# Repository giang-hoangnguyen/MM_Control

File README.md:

# MM_Control

Board điều khiển chuyển động dùng STM32F407VET6, 100 × 100 mm, 2 lớp. Một board gồm 4 kênh động cơ DC (DRV8872), 3 socket driver bước TMC2209, cổng bus servo STS3215, USB-C (CDC), CAN và các header SPI, I2C, UART.

Repo gồm hồ sơ thiết kế (KiCad, Gerber, BOM), firmware, thư viện Python, vỏ in 3D và tài liệu hướng dẫn đặt mạch, mua linh kiện, hàn, kiểm tra, ứng dụng. Tác giả thiết kế: tue-minh. Chỉnh sửa và bổ sung: giang-hoangnguyen.

## Bắt đầu

1. Đọc hướng dẫn chi tiết tại [docs/MM_Control_Hướng dẫn.pdf](docs/MM_Control_H%C6%B0%E1%BB%9Bng%20d%E1%BA%ABn.pdf) và [docs/MM_Control_Hướng dẫn.pptx](docs/MM_Control_H%C6%B0%E1%BB%9Bng%20d%E1%BA%ABn.pptx).
2. Đặt PCB bằng [hardware/MM_Control_gerber.zip](hardware/MM_Control_gerber.zip): 2 lớp, 100 × 100 mm, 1,6 mm.
3. Mua linh kiện theo [hardware/BOM_MM_Control.csv](hardware/BOM_MM_Control.csv), thêm 3 module TMC2209, động cơ, nguồn, ST-Link, cáp USB-C dữ liệu.
4. Hàn theo 4 giai đoạn (nguồn 5 V, 3,3 V, MCU và USB, driver). Chỉnh RV1 cho TP3 = 5,0 V **trước khi** gắn linh kiện 5 V.
5. Nạp firmware (`firmware/build/Debug/MM_Control.bin` tại 0x08000000) bằng ST-Link qua J3.
6. Test từng khối bằng ví dụ Python trong `firmware/python/examples`.

## Cấp nguồn

| Mục | Giá trị | Cơ sở |
|---|---|---|
| VM dùng được | 6,5–28 V | DRV8872 ≥ 6,5 V, TMC2209 ≤ 28 V (datasheet) |
| Dòng chop mỗi kênh DC | khoảng 1,75 A | 0,35 V / 0,2 Ω (datasheet DRV8872, tự tính) |
| TMC2209 | 2 A RMS mỗi cuộn | datasheet |
| Buck 5 V | 3 A | datasheet TPS5430 |
| Servo STS3215 | bản 7,4 V: 4–7,4 V; có bản 12 V | datasheet Feetech; dùng chung rail VM |

Board không có mạch chống ngược cực trên VM. USB-C không cấp nguồn cho board.

## Cấu trúc thư mục

```
docs/        Hướng dẫn chi tiết (PDF, Word), slide hướng dẫn
hardware/    Gerber, BOM, schematic PDF, dự án KiCad 9
firmware/    Mã nguồn STM32 (CMake), thư viện Python, file .bin dựng sẵn
enclosure/   Vỏ in 3D: STL (hướng in), file Fusion, script dựng vỏ
images/      Ảnh dùng trong tài liệu
```

## Vỏ in 3D

Hộp hai mảnh, kẹp board bằng 4 vít M4 × 12 qua lỗ góc, 4 insert M4 trong trụ nắp. In PLA.

## Nguồn và giấy phép

- Datasheet: TI DRV8872, TPS5430; Trinamic TMC2209; Feetech STS3215 (liên kết trong tài liệu chi tiết, mục 9).
- Repo không kèm file LICENSE.

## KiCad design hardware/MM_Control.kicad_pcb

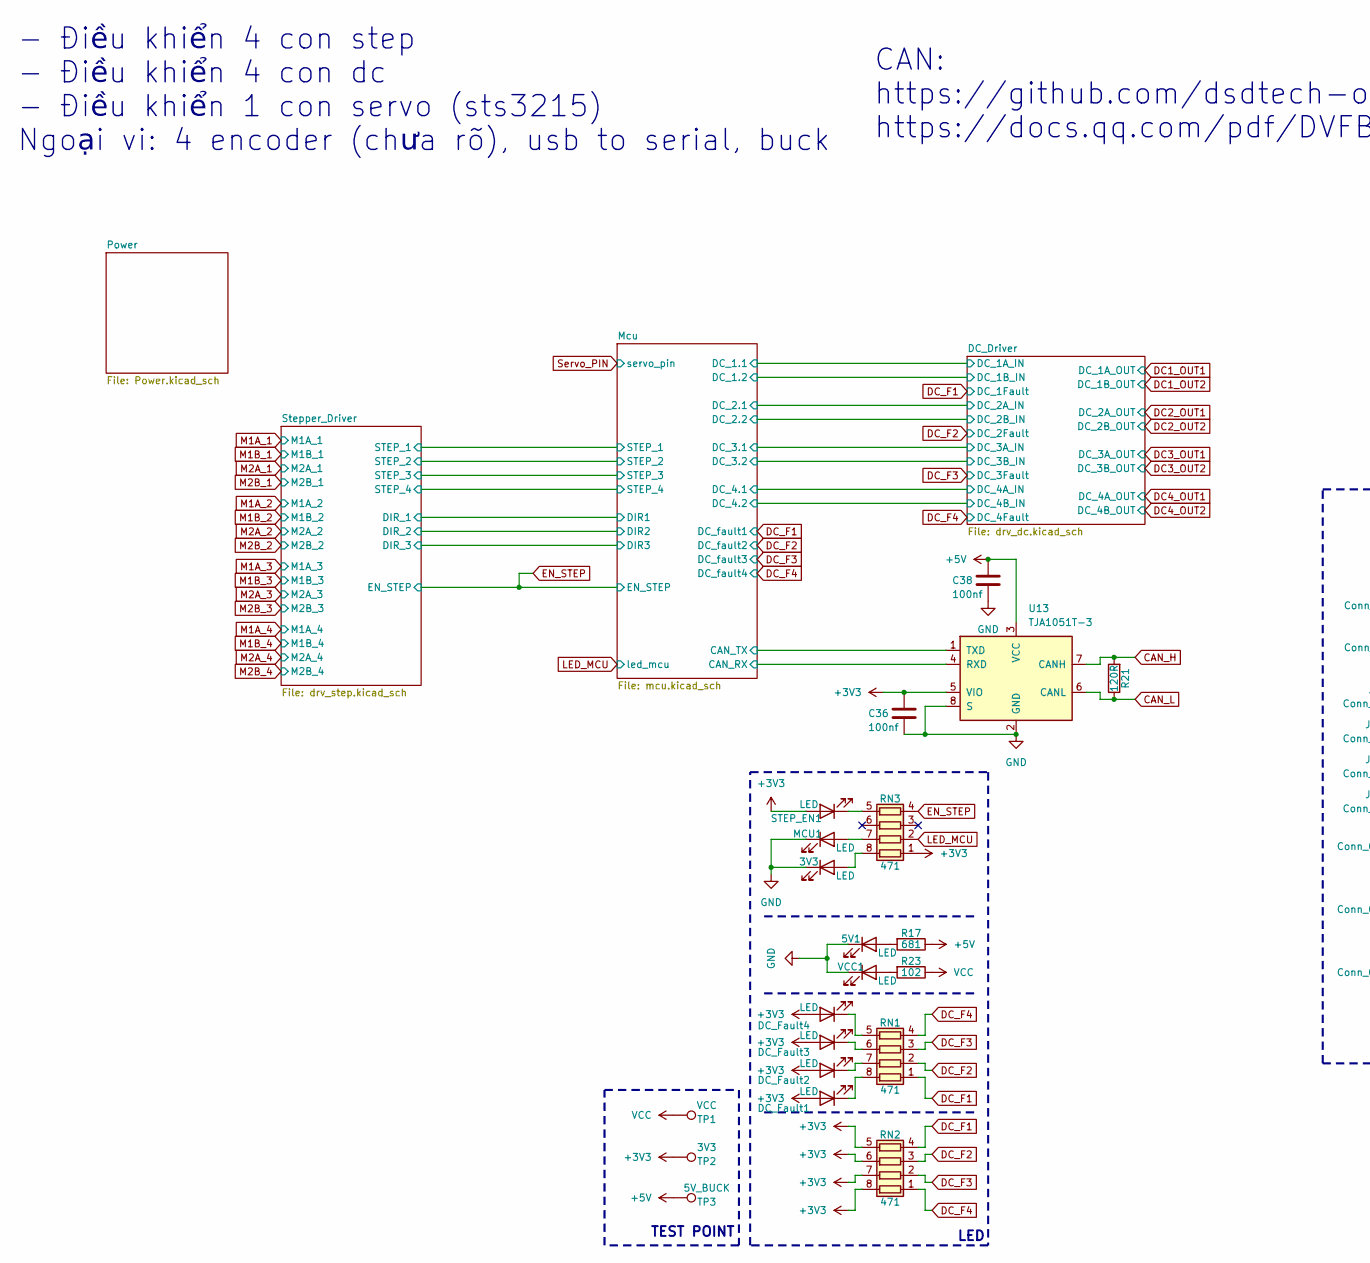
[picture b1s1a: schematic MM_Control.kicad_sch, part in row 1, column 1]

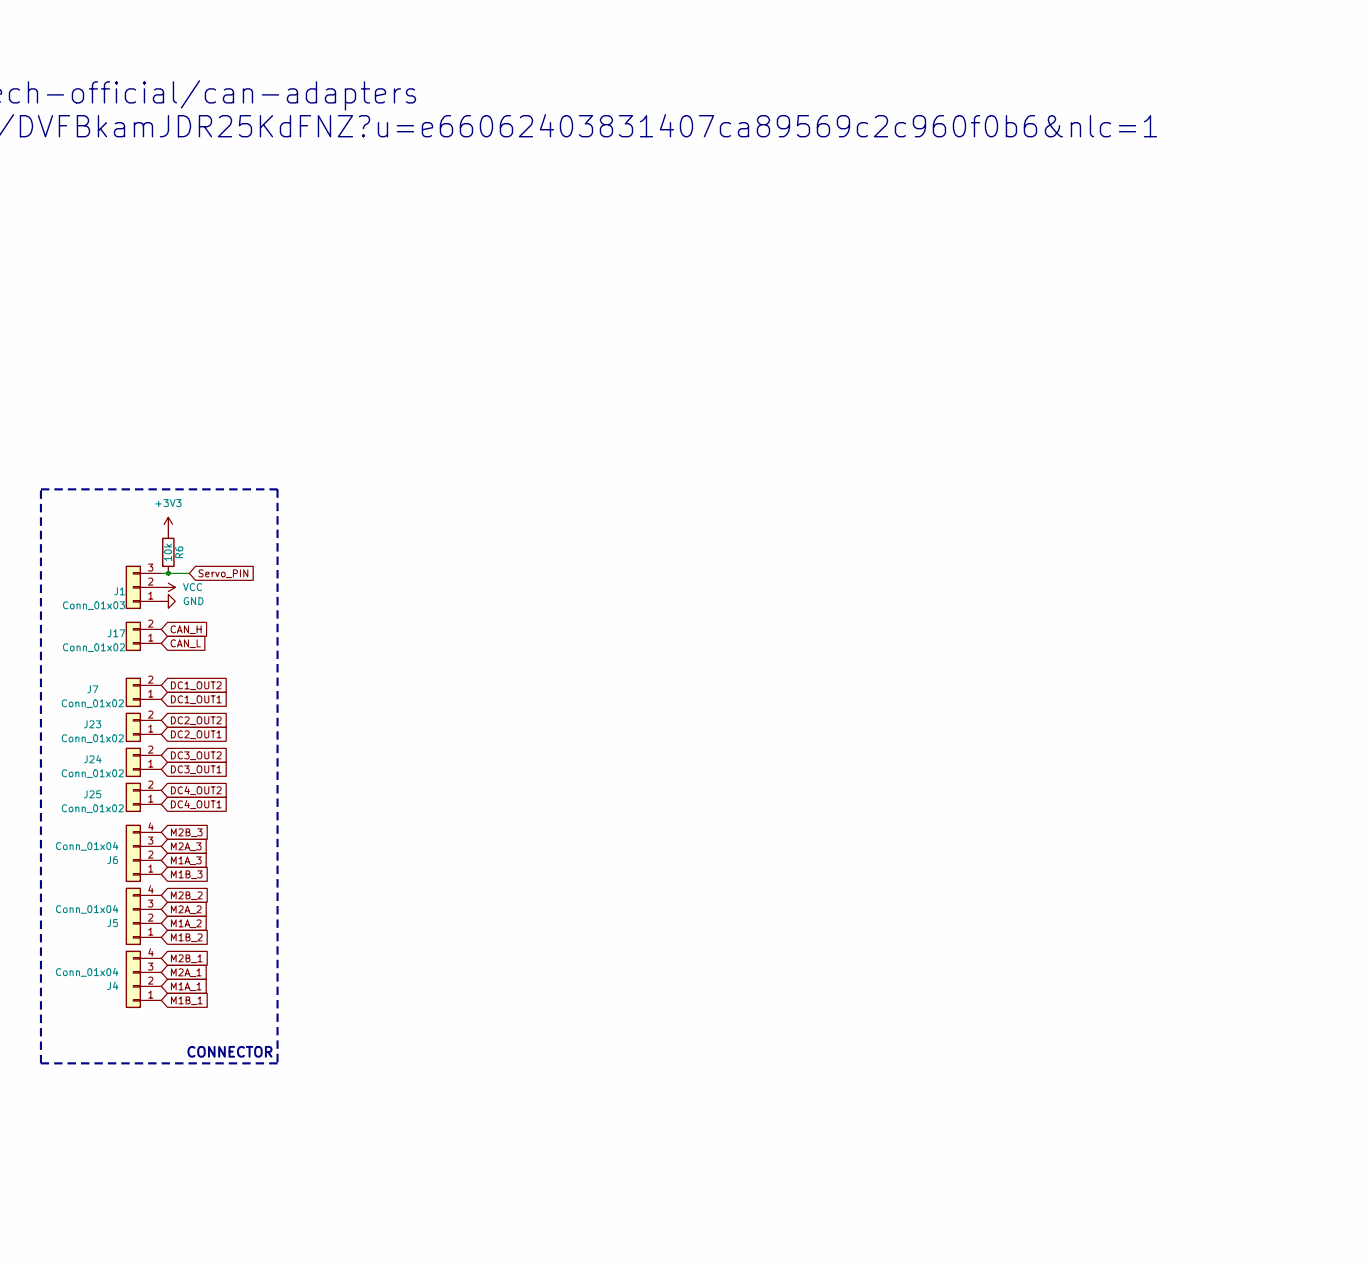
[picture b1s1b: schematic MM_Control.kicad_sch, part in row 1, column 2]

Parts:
3V3, 5V1: LED; LED_0603_1608Metric_Pad1.05x0.95mm_HandSolder
C36, C38: 100nf; C_0603_1608Metric_Pad1.08x0.95mm_HandSolder
DC_Fault1, DC_Fault2, DC_Fault3, DC_Fault4: LED; LED_0603_1608Metric_Pad1.05x0.95mm_HandSolder
J1: Conn_01x03; Molex_SPOX_5267-03A_1x03_P2.50mm_Vertical
J4, J5, J6: Conn_01x04; JST_XH_B4B-XH-A_1x04_P2.50mm_Vertical
J7, J23, J24, J25: Conn_01x02; TerminalBlock_Phoenix_MKDS-1,5-2-5.08_1x02_P5.08mm_Horizont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
J17: Conn_01x02; TerminalBlock_MaiXu_MX126-5.0-02P_1x02_P5.00mm
MCU1: LED; LED_0603_1608Metric_Pad1.05x0.95mm_HandSolder
R6: 10k; R_0603_1608Metric_Pad0.98x0.95mm_HandSolder
R17: 681; R_0603_1608Metric_Pad0.98x0.95mm_HandSolder
R21: 120R; R_0603_1608Metric_Pad0.98x0.95mm_HandSolder
R23: 102; R_0603_1608Metric_Pad0.98x0.95mm_HandSolder
RN1, RN2, RN3: 471; R_Array_Concave_4x0603
STEP_EN1: LED; LED_0603_1608Metric_Pad1.05x0.95mm_HandSolder
TP1: VCC; TestPoint_Pad_D2.0mm
TP2: 3V3; TestPoint_Pad_D2.0mm
TP3: 5V_BUCK; TestPoint_Pad_D2.0mm
U13: TJA1051T-3; SOIC-8_3.9x4.9mm_P1.27mm
VCC1: LED; LED_0603_1608Metric_Pad1.05x0.95mm_HandSolder

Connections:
+3V3: C36.2, DC_Fault1.2 (A), DC_Fault2.2 (A), DC_Fault3.2 (A), DC_Fault4.2 (A), R6.1, RN2.5 (R4.2), RN2.6 (R3.2), RN2.7 (R2.2), RN2.8 (R1.2), RN3.1 (R1.1), STEP_EN1.2 (A), TP2.1, U13.5 (VIO); also elsewhere on the board
+5V: C38.2, R17.1, TP3.1, U13.3 (VCC); also elsewhere on the board
/Mcu/CAN_RX: U13.4 (RXD); also elsewhere on the board
/Mcu/CAN_TX: U13.1 (TXD); also elsewhere on the board
CAN_H: J17.2, R21.2, U13.7 (CANH)
CAN_L: J17.1, R21.1, U13.6 (CANL)
DC1_OUT1: J7.1; also elsewhere on the board
DC1_OUT2: J7.2; also elsewhere on the board
DC2_OUT1: J23.1; also elsewhere on the board
DC2_OUT2: J23.2; also elsewhere on the board
DC3_OUT1: J24.1; also elsewhere on the board
DC3_OUT2: J24.2; also elsewhere on the board
DC4_OUT1: J25.1; also elsewhere on the board
DC4_OUT2: J25.2; also elsewhere on the board
DC_F1: RN1.1 (R1.1), RN2.4 (R4.1); also elsewhere on the board
DC_F2: RN1.2 (R2.1), RN2.3 (R3.1); also elsewhere on the board
DC_F3: RN1.3 (R3.1), RN2.2 (R2.1); also elsewhere on the board
DC_F4: RN1.4 (R4.1), RN2.1 (R1.1); also elsewhere on the board
EN_STEP: RN3.4 (R4.1); also elsewhere on the board
GND: 3V3.1 (K), 5V1.1 (K), C36.1, C38.1, J1.1, MCU1.1 (K), U13.2 (GND), U13.8 (S), VCC1.1 (K); also elsewhere on the board
LED_MCU: RN3.2 (R2.1); also elsewhere on the board
M1A_1: J4.2; also elsewhere on the board
M1A_2: J5.2; also elsewhere on the board
M1A_3: J6.2; also elsewhere on the board
M1B_1: J4.1; also elsewhere on the board
M1B_2: J5.1; also elsewhere on the board
M1B_3: J6.1; also elsewhere on the board
M2A_1: J4.3; also elsewhere on the board
M2A_2: J5.3; also elsewhere on the board
M2A_3: J6.3; also elsewhere on the board
M2B_1: J4.4; also elsewhere on the board
M2B_2: J5.4; also elsewhere on the board
M2B_3: J6.4; also elsewhere on the board
unnamed: 3V3.2 (A), RN3.8 (R1.2)
unnamed: 5V1.2 (A), R17.2
unnamed: DC_Fault1.1 (K), RN1.8 (R1.2)
unnamed: DC_Fault2.1 (K), RN1.7 (R2.2)
unnamed: DC_Fault3.1 (K), RN1.6 (R3.2)
unnamed: DC_Fault4.1 (K), RN1.5 (R4.2)
unnamed: MCU1.2 (A), RN3.7 (R2.2)
unnamed: RN3.5 (R4.2), STEP_EN1.1 (K)
unnamed: R23.2, VCC1.2 (A)
Servo_PIN: J1.3, R6.2; also elsewhere on the board
VM1: J1.2, R23.1, TP1.1; also elsewhere on the board

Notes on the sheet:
TEST POINT
CAN: https://github.com/dsdtech-official/can-adapters https://docs.qq.com/pdf/DVFBkamJDR25KdFNZ?u=e66062403831407ca89569c2c960f0b6&nlc=1
CONNECTOR
LED
- Điều khiển 4 con step - Điều khiển 4 con dc - Điều khiển 1 con servo (sts3215) Ngoại vi: 4 encoder (chưa rõ), usb to serial, buck

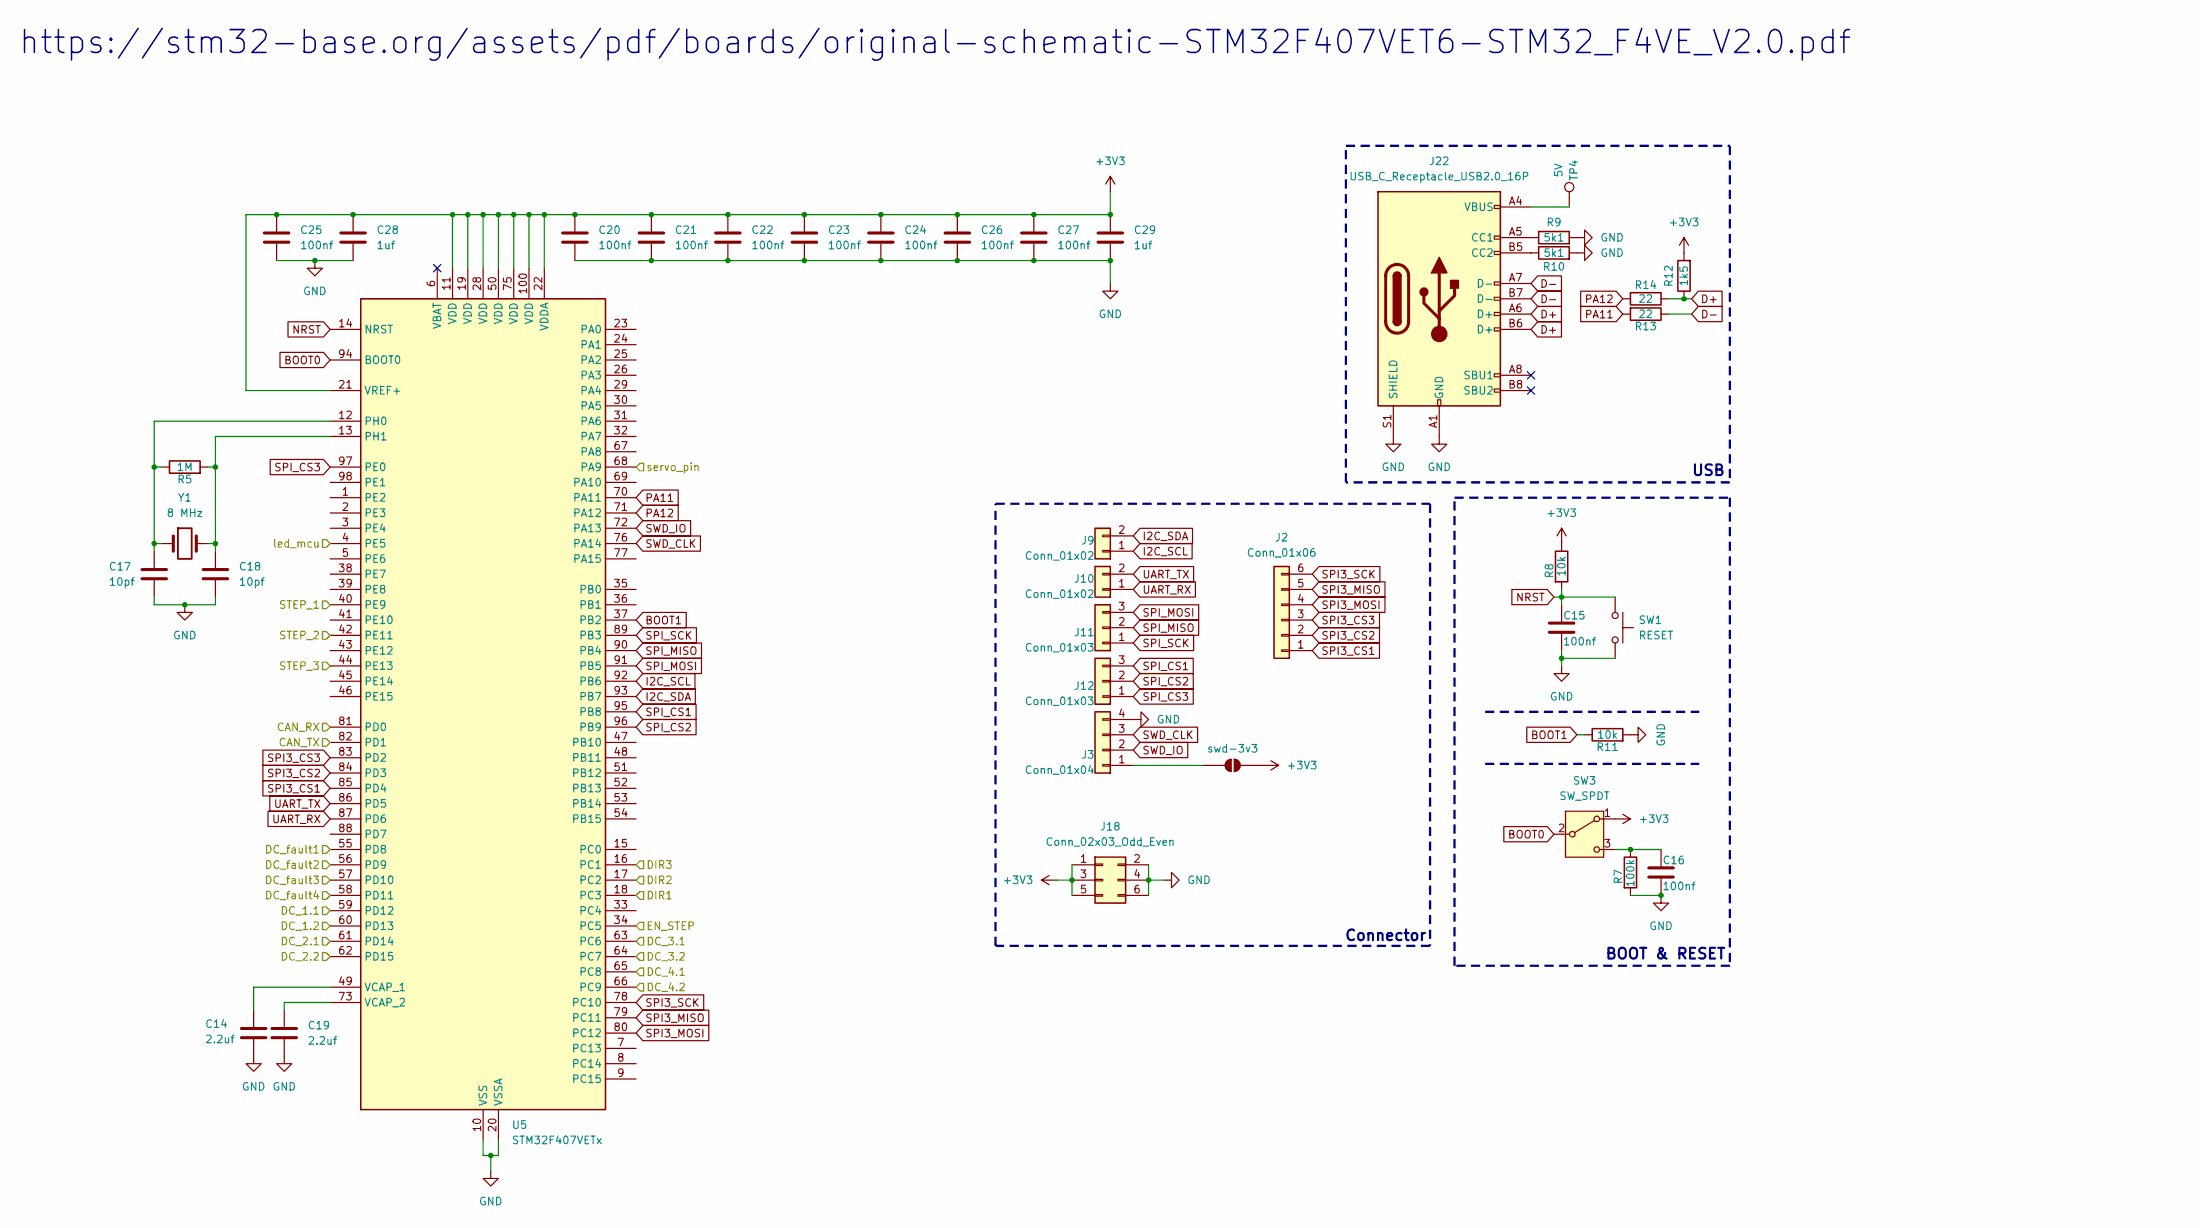
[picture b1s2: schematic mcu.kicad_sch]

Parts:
C14, C19: 2.2uf; C_0603_1608Metric_Pad1.08x0.95mm_HandSolder
C15, C16, C20, C21, C22, C23, C24, C25, C26, C27: 100nf; C_0603_1608Metric_Pad1.08x0.95mm_HandSolder
C17, C18: 10pf; C_0603_1608Metric_Pad1.08x0.95mm_HandSolder
C28, C29: 1uf; C_0603_1608Metric_Pad1.08x0.95mm_HandSolder
J2: Conn_01x06; PinHeader_1x06_P2.54mm_Vertical
J3: Conn_01x04; PinHeader_1x04_P2.54mm_Vertical
J9, J10: Conn_01x02; PinHeader_1x02_P2.54mm_Vertical
J11, J12: Conn_01x03; PinHeader_1x03_P2.54mm_Vertical
J18: Conn_02x03_Odd_Even; PinHeader_2x03_P2.54mm_Vertical
J22: USB_C_Receptacle_USB2.0_16P; USB_C_Receptacle_GCT_USB4105-xx-A_16P_TopMnt_Horizontal
R5: 1M; R_0603_1608Metric_Pad0.98x0.95mm_HandSolder
R7: 100k; R_0603_1608Metric_Pad0.98x0.95mm_HandSolder
R8, R11: 10k; R_0603_1608Metric_Pad0.98x0.95mm_HandSolder
R9, R10: 5k1; R_0603_1608Metric_Pad0.98x0.95mm_HandSolder
R12: 1k5; R_0603_1608Metric_Pad0.98x0.95mm_HandSolder
R13, R14: 22; R_0603_1608Metric_Pad0.98x0.95mm_HandSolder
SW1: RESET; tue_sw_smd_3x6x2.5mm
SW3: SW_SPDT; tue_SS12D00_3P_2.5mm
TP4: 5V; TestPoint_Pad_D2.0mm
U5: STM32F407VETx; LQFP-100_14x14mm_P0.5mm
Y1: 8 MHz; Crystal_HC49-4H_Vertical
swd-3v3: SolderJumper_2_Open; SolderJumper-2_P1.3mm_Open_RoundedPad1.0x1.5mm

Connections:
+3V3: C20.1, C21.1, C22.1, C23.1, C24.1, C25.1, C26.1, C27.1, C28.1, C29.1, J18.1, J18.3, J18.5, R8.1, R12.2, SW3.1 (A), U5.11 (VDD), U5.19 (VDD), U5.21 (VREF+), U5.22 (VDDA), U5.28 (VDD), U5.50 (VDD), U5.75 (VDD), U5.100 (VDD), swd-3v3.2 (B); also elsewhere on the board
/DC_Driver/DC_1A_IN: U5.59 (PD12); also elsewhere on the board
/DC_Driver/DC_1B_IN: U5.60 (PD13); also elsewhere on the board
/DC_Driver/DC_2A_IN: U5.61 (PD14); also elsewhere on the board
/DC_Driver/DC_2B_IN: U5.62 (PD15); also elsewhere on the board
/DC_Driver/DC_3A_IN: U5.63 (PC6); also elsewhere on the board
/DC_Driver/DC_3B_IN: U5.64 (PC7); also elsewhere on the board
/DC_Driver/DC_4A_IN: U5.65 (PC8); also elsewhere on the board
/DC_Driver/DC_4B_IN: U5.66 (PC9); also elsewhere on the board
/Mcu/CAN_RX: U5.81 (PD0); also elsewhere on the board
/Mcu/CAN_TX: U5.82 (PD1); also elsewhere on the board
/Mcu/DIR1: U5.18 (PC3); also elsewhere on the board
/Mcu/DIR2: U5.17 (PC2); also elsewhere on the board
/Mcu/DIR3: U5.16 (PC1); also elsewhere on the board
/Mcu/STEP_1: U5.40 (PE9); also elsewhere on the board
/Mcu/STEP_2: U5.42 (PE11); also elsewhere on the board
/Mcu/STEP_3: U5.44 (PE13); also elsewhere on the board
BOOT0: SW3.2 (B), U5.94 (BOOT0)
BOOT1: R11.1, U5.37 (PB2)
D+: J22.A6 (D+), J22.B6 (D+), R12.1, R14.1
D-: J22.A7 (D-), J22.B7 (D-), R13.1
DC_F1: U5.55 (PD8); also elsewhere on the board
DC_F2: U5.56 (PD9); also elsewhere on the board
DC_F3: U5.57 (PD10); also elsewhere on the board
DC_F4: U5.58 (PD11); also elsewhere on the board
EN_STEP: U5.34 (PC5); also elsewhere on the board
GND: C14.2, C15.2, C16.2, C17.1, C18.2, C19.2, C20.2, C21.2, C22.2, C23.2, C24.2, C25.2, C26.2, C27.2, C28.2, C29.2, J3.4, J18.2, J18.4, J18.6, J22.A1 (GND), J22.A12 (GND), J22.B1 (GND), J22.B12 (GND), J22.S1 (SHIELD), R7.2, R9.2, R10.2, R11.2, SW1.2, U5.10 (VSS), U5.20 (VSSA), U5.27 (VSS), U5.74 (VSS), U5.99 (VSS); also elsewhere on the board
I2C_SCL: J9.1, U5.92 (PB6)
I2C_SDA: J9.2, U5.93 (PB7)
LED_MCU: U5.4 (PE5); also elsewhere on the board
NRST: C15.1, R8.2, SW1.1, U5.14 (NRST)
unnamed: J3.1, swd-3v3.1 (A)
unnamed: J22.A5 (CC1), R9.1
unnamed: J22.B5 (CC2), R10.1
unnamed: J22.A4 (VBUS), J22.A9 (VBUS), J22.B4 (VBUS), J22.B9 (VBUS), TP4.1
unnamed: C16.1, R7.1, SW3.3 (C)
unnamed: C17.2, R5.1, U5.12 (PH0), Y1.1
unnamed: C18.1, R5.2, U5.13 (PH1), Y1.2
unnamed: C14.1, U5.49 (VCAP_1)
unnamed: C19.1, U5.73 (VCAP_2)
PA11: R13.2, U5.70 (PA11)
PA12: R14.2, U5.71 (PA12)
SPI3_CS1: J2.1, U5.85 (PD4)
SPI3_CS2: J2.2, U5.84 (PD3)
SPI3_CS3: J2.3, U5.83 (PD2)
SPI3_MISO: J2.5, U5.79 (PC11)
SPI3_MOSI: J2.4, U5.80 (PC12)
SPI3_SCK: J2.6, U5.78 (PC10)
SPI_CS1: J12.3, U5.95 (PB8)
SPI_CS2: J12.2, U5.96 (PB9)
SPI_CS3: J12.1, U5.97 (PE0)
SPI_MISO: J11.2, U5.90 (PB4)
SPI_MOSI: J11.3, U5.91 (PB5)
SPI_SCK: J11.1, U5.89 (PB3)
SWD_CLK: J3.3, U5.76 (PA14)
SWD_IO: J3.2, U5.72 (PA13)
Servo_PIN: U5.68 (PA9); also elsewhere on the board
UART_RX: J10.1, U5.87 (PD6)
UART_TX: J10.2, U5.86 (PD5)

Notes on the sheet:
Connector
https://stm32-base.org/assets/pdf/boards/original-schematic-STM32F407VET6-STM32_F4VE_V2.0.pdf
BOOT & RESET
USB

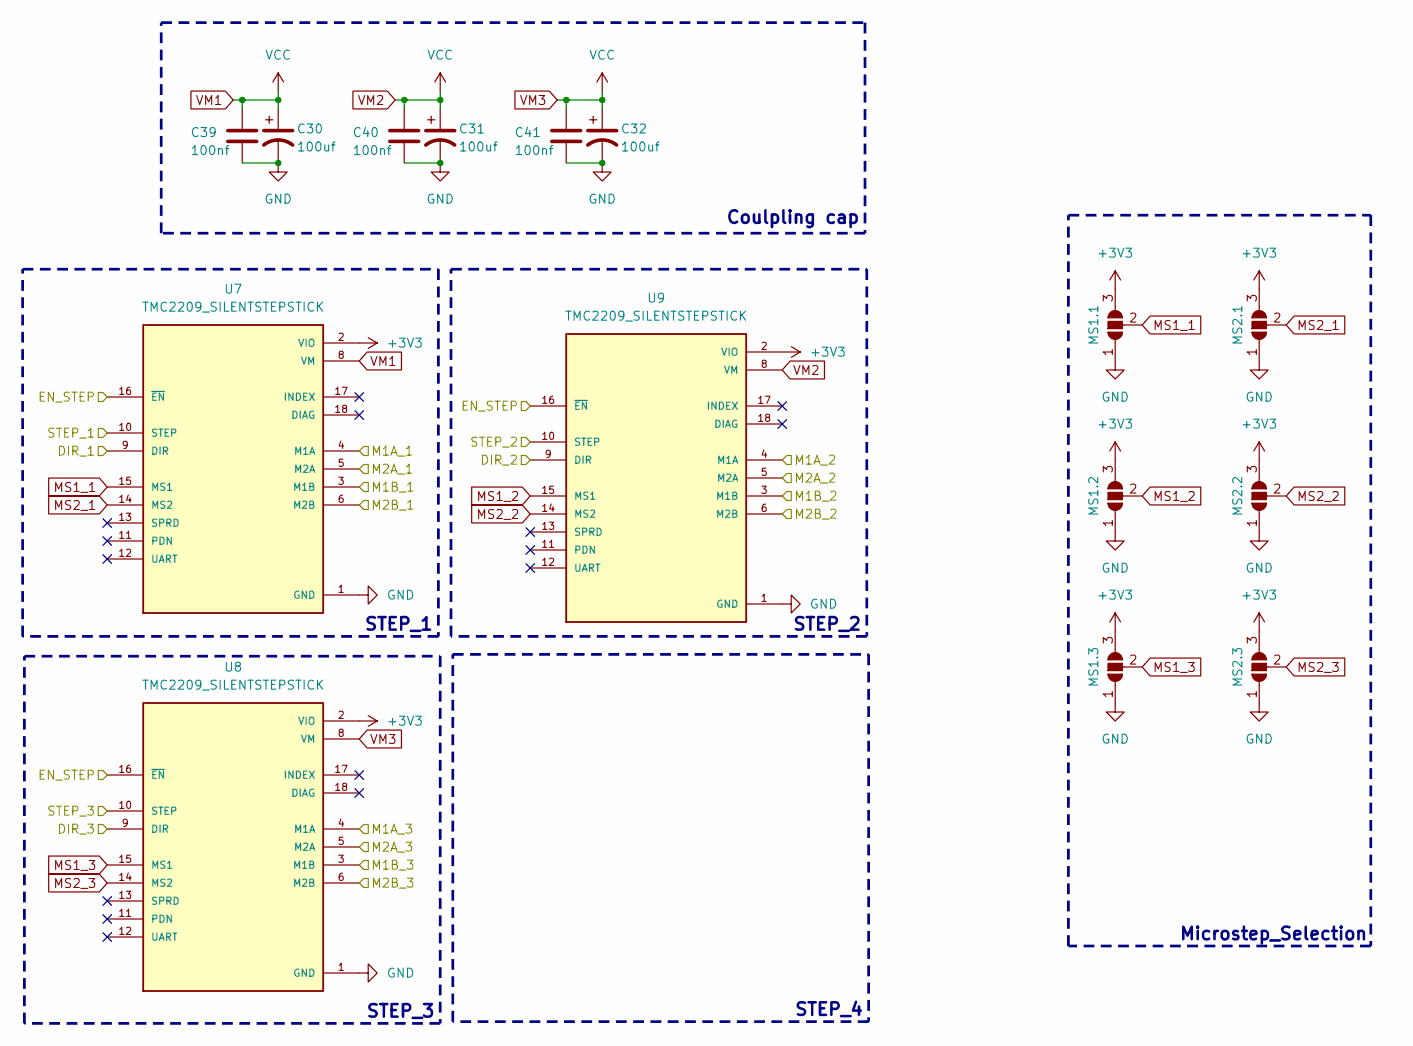
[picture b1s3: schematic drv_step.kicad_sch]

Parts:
C30, C31, C32: 100uf; CP_Elec_6.3x5.9
C39, C40, C41: 100nf; C_1206_3216Metric_Pad1.33x1.80mm_HandSolder
MS1.1, MS1.2, MS1.3, MS2.1, MS2.2, MS2.3: MicroStep_Selection; SolderJumper-3_P1.3mm_Open_RoundedPad1.0x1.5mm
U7, U8, U9: TMC2209_SILENTSTEPSTICK; tue_TMC2209; PARTREV 1.20

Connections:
+3V3: MS1.1.3 (B), MS1.2.3 (B), MS1.3.3 (B), MS2.1.3 (B), MS2.2.3 (B), MS2.3.3 (B), U7.2 (VIO), U8.2 (VIO), U9.2 (VIO); also elsewhere on the board
/Mcu/DIR1: U7.9 (DIR); also elsewhere on the board
/Mcu/DIR2: U9.9 (DIR); also elsewhere on the board
/Mcu/DIR3: U8.9 (DIR); also elsewhere on the board
/Mcu/STEP_1: U7.10 (STEP); also elsewhere on the board
/Mcu/STEP_2: U9.10 (STEP); also elsewhere on the board
/Mcu/STEP_3: U8.10 (STEP); also elsewhere on the board
EN_STEP: U7.16 (~EN), U8.16 (~EN), U9.16 (~EN); also elsewhere on the board
GND: C30.2, C31.2, C32.2, C39.1, C40.1, C41.1, MS1.1.1 (A), MS1.2.1 (A), MS1.3.1 (A), MS2.1.1 (A), MS2.2.1 (A), MS2.3.1 (A), U7.1 (GND), U7.7 (GND), U8.1 (GND), U8.7 (GND), U9.1 (GND), U9.7 (GND); also elsewhere on the board
M1A_1: U7.4 (M1A); also elsewhere on the board
M1A_2: U9.4 (M1A); also elsewhere on the board
M1A_3: U8.4 (M1A); also elsewhere on the board
M1B_1: U7.3 (M1B); also elsewhere on the board
M1B_2: U9.3 (M1B); also elsewhere on the board
M1B_3: U8.3 (M1B); also elsewhere on the board
M2A_1: U7.5 (M2A); also elsewhere on the board
M2A_2: U9.5 (M2A); also elsewhere on the board
M2A_3: U8.5 (M2A); also elsewhere on the board
M2B_1: U7.6 (M2B); also elsewhere on the board
M2B_2: U9.6 (M2B); also elsewhere on the board
M2B_3: U8.6 (M2B); also elsewhere on the board
MS1_1: MS1.1.2 (C), U7.15 (MS1)
MS1_2: MS1.2.2 (C), U9.15 (MS1)
MS1_3: MS1.3.2 (C), U8.15 (MS1)
MS2_1: MS2.1.2 (C), U7.14 (MS2)
MS2_2: MS2.2.2 (C), U9.14 (MS2)
MS2_3: MS2.3.2 (C), U8.14 (MS2)
VM1: C30.1, C31.1, C32.1, C39.2, C40.2, C41.2, U7.8 (VM), U8.8 (VM), U9.8 (VM); also elsewhere on the board

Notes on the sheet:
STEP_4
STEP_1
Coulpling cap
STEP_3
Microstep_Selection
STEP_2

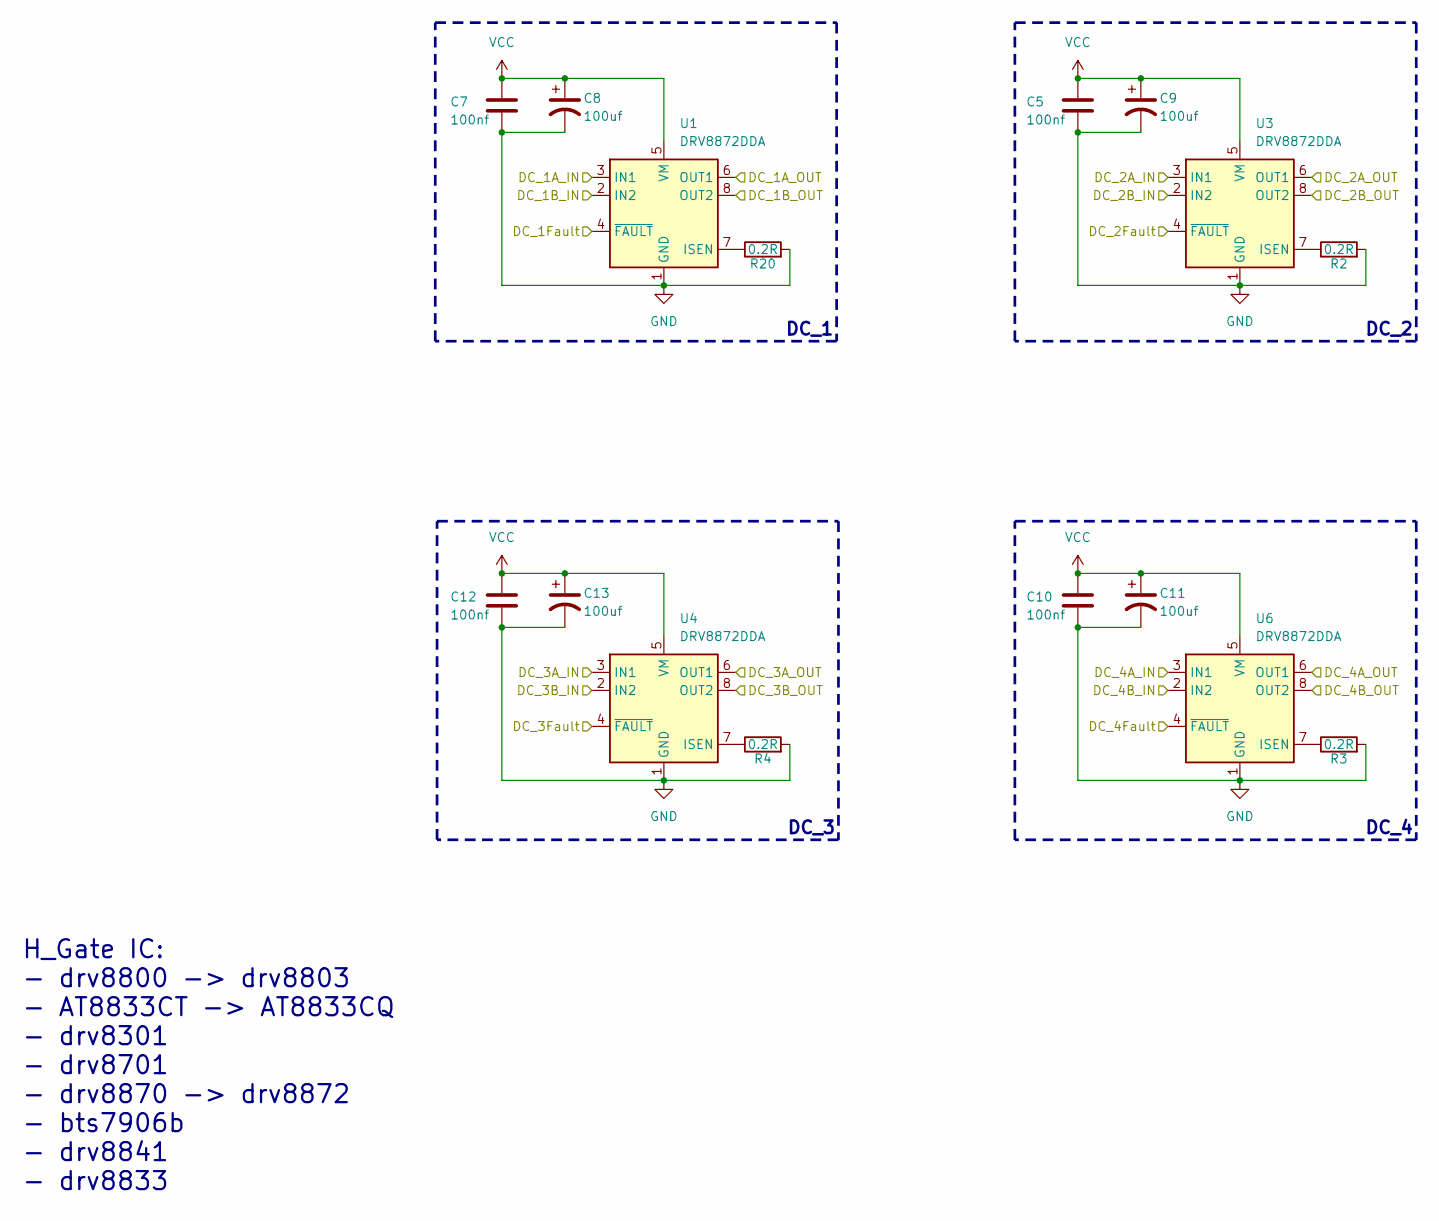
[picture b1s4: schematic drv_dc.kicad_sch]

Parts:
C5, C7, C10, C12: 100nf; C_1206_3216Metric_Pad1.33x1.80mm_HandSolder
C8, C9, C11, C13: 100uf; CP_Elec_6.3x5.9
R2, R3, R4, R20: 0.2R; R_2512_6332Metric_Pad1.40x3.35mm_HandSolder
U1, U3, U4, U6: DRV8872DDA; Texas_HTSOP-8-1EP_3.9x4.9mm_P1.27mm_EP2.95x4.9mm_Mask2.4x3.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

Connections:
/DC_Driver/DC_1A_IN: U1.3 (IN1); also elsewhere on the board
/DC_Driver/DC_1B_IN: U1.2 (IN2); also elsewhere on the board
/DC_Driver/DC_2A_IN: U3.3 (IN1); also elsewhere on the board
/DC_Driver/DC_2B_IN: U3.2 (IN2); also elsewhere on the board
/DC_Driver/DC_3A_IN: U4.3 (IN1); also elsewhere on the board
/DC_Driver/DC_3B_IN: U4.2 (IN2); also elsewhere on the board
/DC_Driver/DC_4A_IN: U6.3 (IN1); also elsewhere on the board
/DC_Driver/DC_4B_IN: U6.2 (IN2); also elsewhere on the board
DC1_OUT1: U1.6 (OUT1); also elsewhere on the board
DC1_OUT2: U1.8 (OUT2); also elsewhere on the board
DC2_OUT1: U3.6 (OUT1); also elsewhere on the board
DC2_OUT2: U3.8 (OUT2); also elsewhere on the board
DC3_OUT1: U4.6 (OUT1); also elsewhere on the board
DC3_OUT2: U4.8 (OUT2); also elsewhere on the board
DC4_OUT1: U6.6 (OUT1); also elsewhere on the board
DC4_OUT2: U6.8 (OUT2); also elsewhere on the board
DC_F1: U1.4 (~FAULT); also elsewhere on the board
DC_F2: U3.4 (~FAULT); also elsewhere on the board
DC_F3: U4.4 (~FAULT); also elsewhere on the board
DC_F4: U6.4 (~FAULT); also elsewhere on the board
GND: C5.1, C7.1, C8.2, C9.2, C10.1, C11.2, C12.1, C13.2, R2.2, R3.2, R4.2, R20.2, U1.1 (GND), U1.9 (GND), U3.1 (GND), U3.9 (GND), U4.1 (GND), U4.9 (GND), U6.1 (GND), U6.9 (GND); also elsewhere on the board
unnamed: R20.1, U1.7 (ISEN)
unnamed: R2.1, U3.7 (ISEN)
unnamed: R4.1, U4.7 (ISEN)
unnamed: R3.1, U6.7 (ISEN)
VM1: C5.2, C7.2, C8.1, C9.1, C10.2, C11.1, C12.2, C13.1, U1.5 (VM), U3.5 (VM), U4.5 (VM), U6.5 (VM); also elsewhere on the board

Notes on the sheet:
DC_3
DC_1
DC_2
H_Gate IC: - drv8800 -> drv8803 - AT8833CT -> AT8833CQ - drv8301 - drv8701 - drv8870 -> drv8872 - bts7906b - drv8841 - drv8833
DC_4

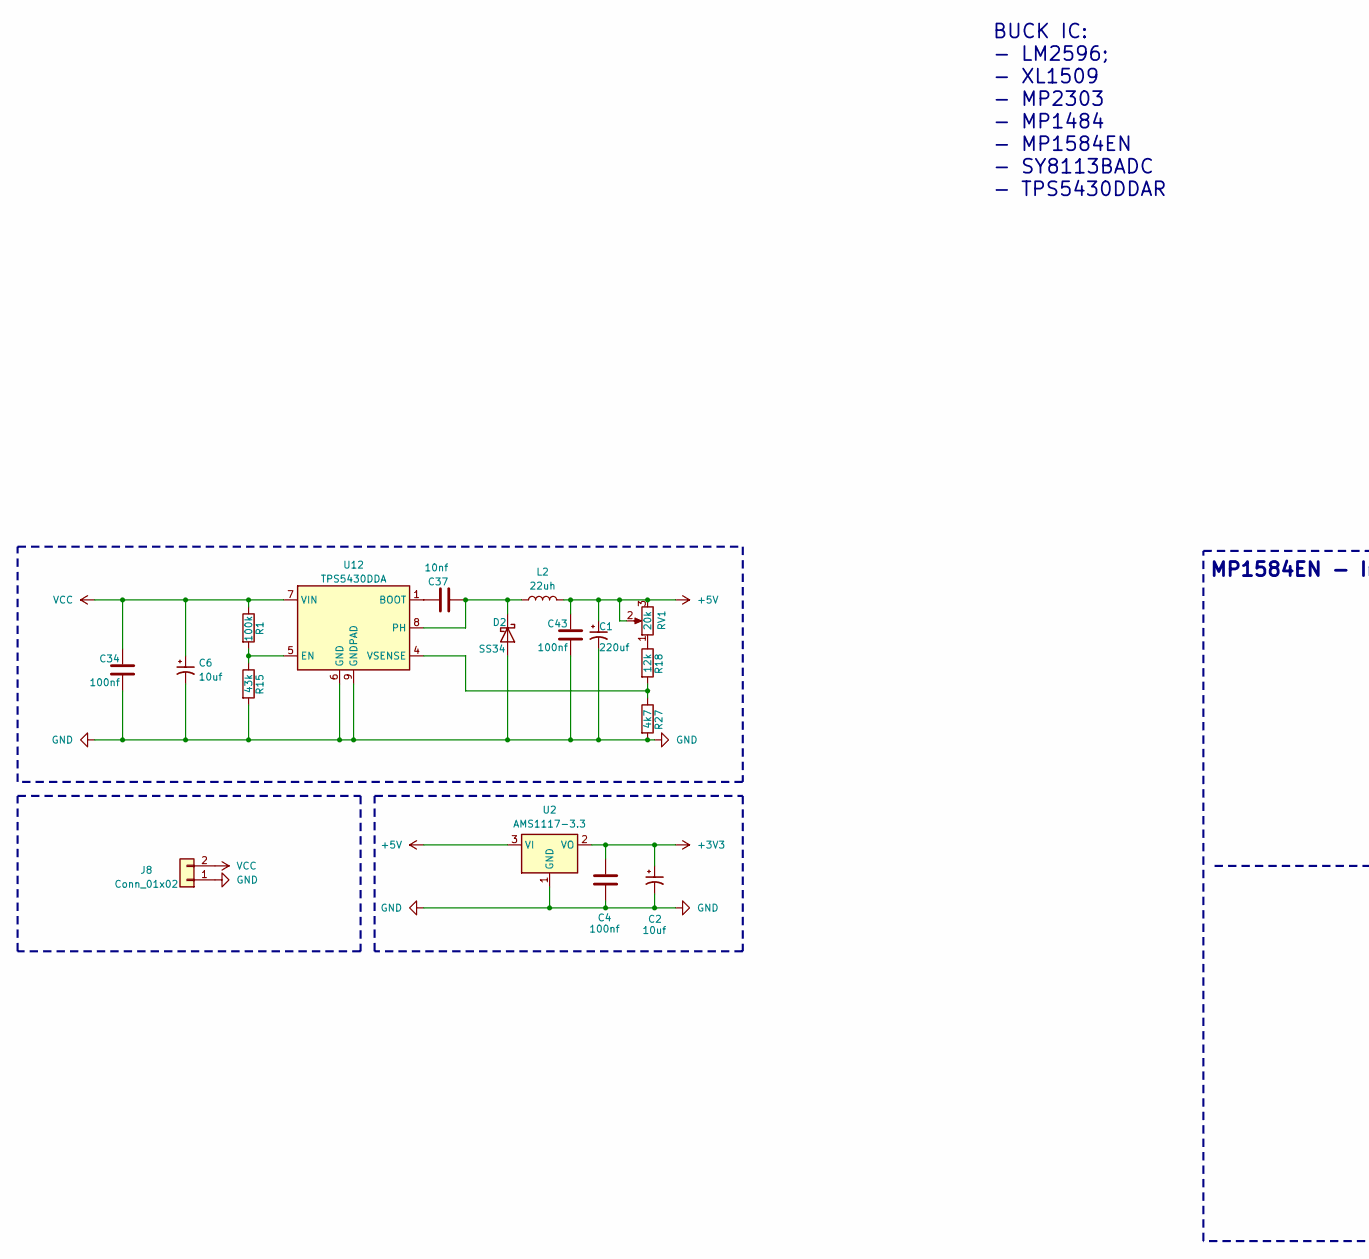
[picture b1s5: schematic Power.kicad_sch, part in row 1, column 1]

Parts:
C1: 220uf; CP_Elec_6.3x7.7
C2, C6: 10uf; CP_EIA-3216-18_Kemet-A_HandSolder
C4, C34, C43: 100nf; C_1206_3216Metric_Pad1.33x1.80mm_HandSolder
C37: 10nf; C_0603_1608Metric_Pad1.08x0.95mm_HandSolder
D2: SS34; D_SMA
J8: Conn_01x02; TerminalBlock_Phoenix_MKDS-1,5-2-5.08_1x02_P5.08mm_Horizont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
L2: 22uh; L_10.4x10.4_H4.8
R1: 100k; R_0603_1608Metric_Pad0.98x0.95mm_HandSolder
R15: 43k; R_0603_1608Metric_Pad0.98x0.95mm_HandSolder
R18: 12k; R_0603_1608Metric_Pad0.98x0.95mm_HandSolder
R27: 4k7; R_0603_1608Metric_Pad0.98x0.95mm_HandSolder
RV1: 20k; Potentiometer_Bourns_3296W_Vertical
U2: AMS1117-3.3; SOT-223-3_TabPin2
U12: TPS5430DDA; TI_SO-PowerPAD-8_ThermalVias

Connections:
+3V3: C2.1, C4.2, U2.2 (VO); also elsewhere on the board
+5V: C1.1, C43.2, L2.2, RV1.2, RV1.3, U2.3 (VI); also elsewhere on the board
GND: C1.2, C2.2, C4.1, C6.2, C34.1, C43.1, D2.2 (A), J8.1, R15.2, R27.2, U2.1 (GND), U12.6 (GND), U12.9 (GNDPAD); also elsewhere on the board
unnamed: C37.1, D2.1 (K), L2.1, U12.8 (PH)
unnamed: R18.1, RV1.1
unnamed: C37.2, U12.1 (BOOT)
unnamed: R1.2, R15.1, U12.5 (EN)
unnamed: R18.2, R27.1, U12.4 (VSENSE)
VM1: C6.1, C34.2, J8.2, R1.1, U12.7 (VIN); also elsewhere on the board

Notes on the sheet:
MP1584EN - Instruction
R=360 (kOhm) -> f=500 (kHz)
BUCK IC: - LM2596; - XL1509 - MP2303 - MP1484 - MP1584EN - SY8113BADC - TPS5430DDAR
